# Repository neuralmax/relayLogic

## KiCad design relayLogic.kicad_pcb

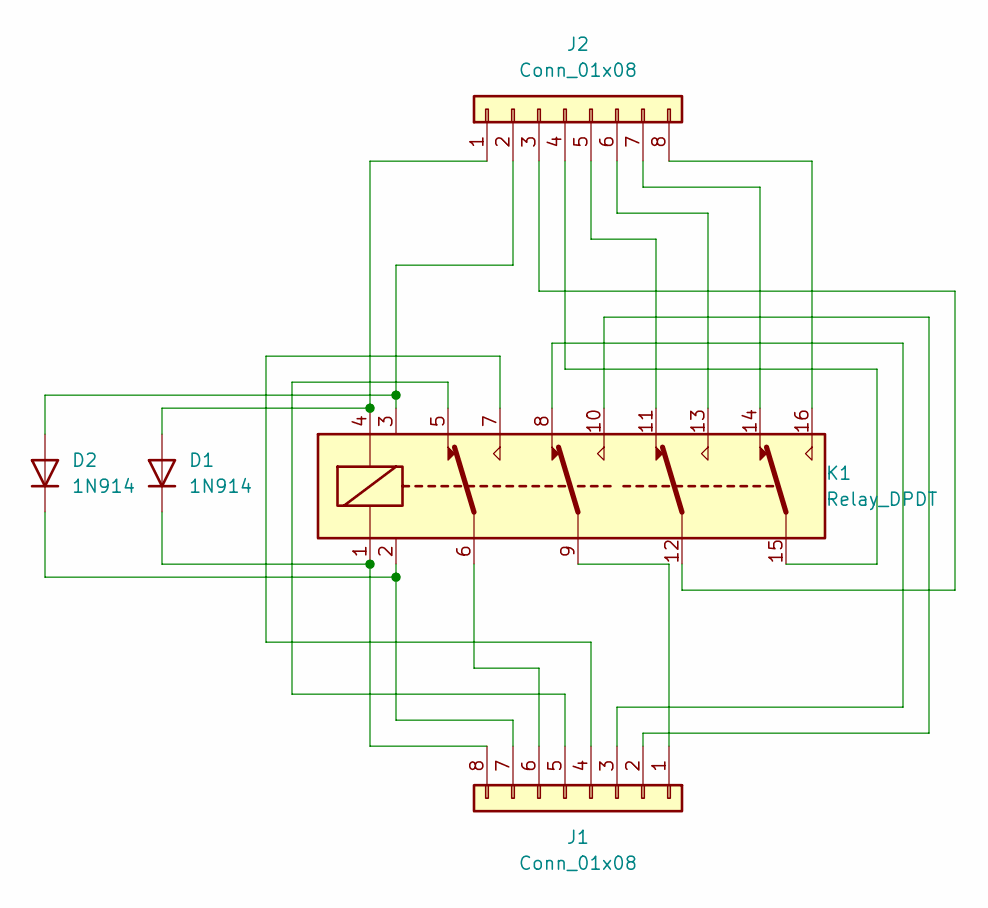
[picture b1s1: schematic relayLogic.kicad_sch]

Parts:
D1, D2: 1N914; D_DO-35_SOD27_P7.62mm_Horizontal
J1, J2: Conn_01x08; PinHeader_1x08_P2.54mm_Vertical
K1: Relay_DPDT; V23154

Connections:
unnamed: D1.2 (A), J2.1, K1.4
unnamed: D1.1 (K), J1.8, K1.1
unnamed: D2.2 (A), J2.2, K1.3
unnamed: D2.1 (K), J1.7, K1.2
unnamed: J1.1, K1.9
unnamed: J1.2, K1.10
unnamed: J1.3, K1.8
unnamed: J1.4, K1.7
unnamed: J1.5, K1.5
unnamed: J1.6, K1.6
unnamed: J2.3, K1.12
unnamed: J2.4, K1.15
unnamed: J2.5, K1.11
unnamed: J2.6, K1.13
unnamed: J2.7, K1.14
unnamed: J2.8, K1.16

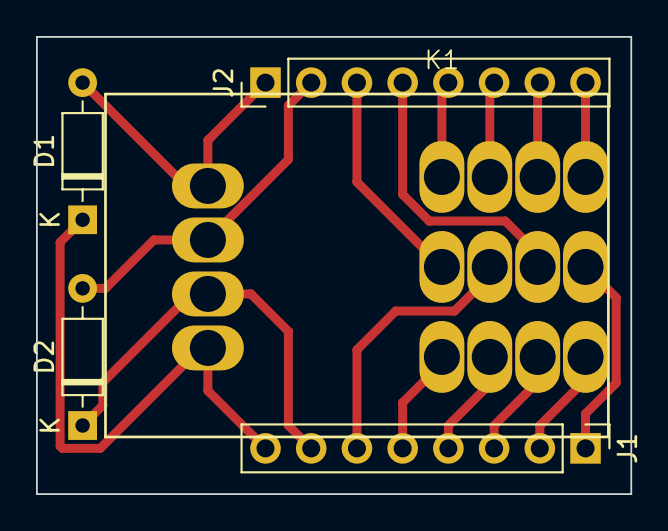
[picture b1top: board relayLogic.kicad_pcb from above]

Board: 2 copper layers, 33.0 x 25.4 mm, 5 parts (0 on the bottom side), 16 nets.

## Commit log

2024-08-23 t init git add README.md git commit -m "first commit" git branch -M main git remote add origin git@github.com:neuralmax/relayLogic.git git init git add README.md git commit -m "first commit" git bran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
